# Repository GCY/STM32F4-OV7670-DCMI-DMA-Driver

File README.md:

# STM32F4-Discovery-OV7670-DCMI-DMA-Driver

STM32F429-DISCO+OV7670 MAC and Linux project with arm-none-eabi-gcc, it is modified from [Individální projekty MPOA](http://www.urel.feec.vutbr.cz/MPOA/2014/cam-ov7670) Keil-C project.

I use the same parameters of OV7670 as STM32F429, but the color will be wrong in my design, maybe the problem is exposure, gain, high-speed clock-signal layout? that is my issue list. [to be fix.](https://www.arducam.com/rgb565-format-issues/)

## DCMI Configuration
| STM32F407 | STM32F429 | OV7670 |
| :----: | :----: | :----: |
| 3V3 | 3V3 | RESET |
| GND | GND | PWDN |
| PC6 | PC6 | D0 |
| PC7 | PC7 | D1 |
| PE0 | PC8 | D2 |
| PE1 | PC9 | D3 |
| PE4 | PE4 | D4 |
| PB6 | PB6 | D5 |
| PE5 | PE5 | D6 |
| PE6 | PE6 | D7 |
| PA8 | PA8 | XCLK |
| PA6 | PA6 | PCLK |
| PA4 | PA4 | HREF |
| PB7 | PB7 | VSYNC |
| PB9 | PB9 | SIOD |
| PB8 | PB8 | SIOC |
| GND | GND | GND |
| 3V3 | 3V3 | 3V3 |

## Build

 1. cd .STM32F429-Discovery-OV7670-DCMI-DMA-Driver/STM32F429 Version/firmware/stm32F429-OV7670 & make
 2. load *.elf file with arm-none-eabi-gdb
 3. run

## Test

 1. First, power on and initialize STM32F429 OV7670 SCCB bus.
 2. When the LCD progress bar is complete, OV7670 SCCB command are initialized.
 3. Push "User" button.
 4. STM32F429 capture frame and display to LCD.

Licensing
=======
Copyright (C) 2020  TonyGUO <https://github.com/GCY>.

This program is free software: you can redistribute it and/or modify
it under the terms of the GNU General Public License as published by
the Free Software Foundation, either version 3 of the License, or
(at your option) any later version.

This program is distributed in the hope that it will be useful,
but WITHOUT ANY WARRANTY; without even the implied warranty of
MERCHANTABILITY or FITNESS FOR A PARTICULAR PURPOSE.  See the
GNU General Public License for more details.

You should have received a copy of the GNU General Public License
along with this program.  If not, see <http://www.gnu.org/licenses/>.

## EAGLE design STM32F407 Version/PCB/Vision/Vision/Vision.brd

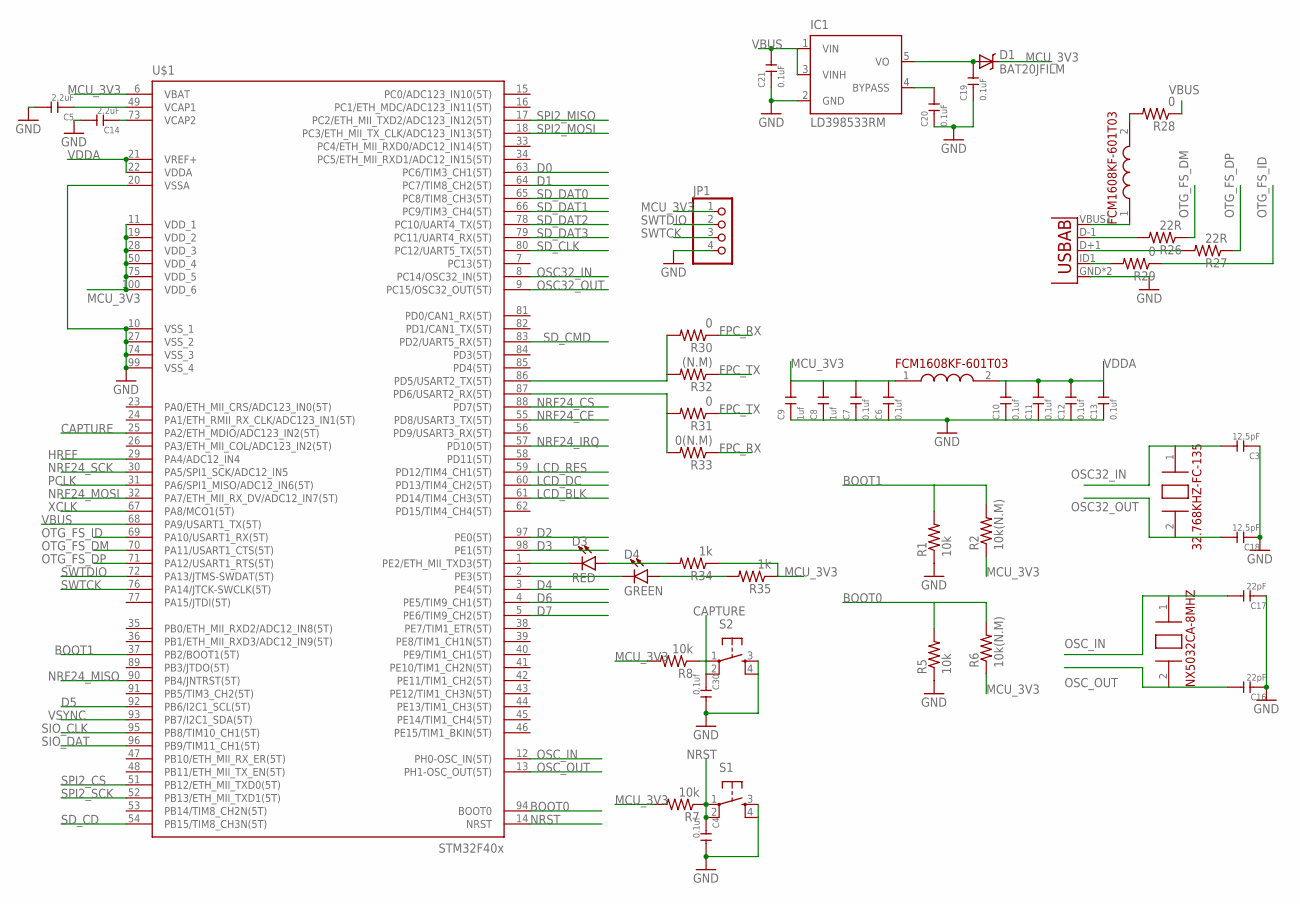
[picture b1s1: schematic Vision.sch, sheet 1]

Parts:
C3, C18: 12.5pF; C0603
C4, C6, C7, C10, C11, C12, C13, C30: 0.1uf; C0603
C5, C14: 2.2uF; C0603
C8, C9: 1uf; C0603
C16, C17: 22pF; C0603
C19, C20, C21: 0.1uF; C0603
D1: BAT20JFILM; SOD-323
D3: RED; LED-0603
D4: GREEN; LED-0603
IC1: LD398533RM; SOT23-5L
JP1: PINHD-1X4; 1X04
R1, R5, R7, R8: 10k; 0603
R2, R6: 10k(N.M); 0603
R26, R27: 22R; 0603-RES
R28, R29: 0; 0603-RES
R30, R31: 0; 0603
R32: (N.M); 0603
R33: 0(N.M); 0603
R34, R35: 1k; 0603
S1, S2: TAC_SWITCHSMD; TACTILE_SWITCH_SMD
U4: USB""; USB-MICRO-SMD
U$1: STM32F407V; TQFP100
U$2: NX5032CA-8MHZ
U$3, U$5: FCM1608KF-601T03
U$4: 32.768KHZ-FC-135

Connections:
BOOT0: R5.2, R6.2, U$1.94 (BOOT0)
BOOT1: R1.2, R2.2, U$1.37 (PB2/BOOT1(5T))
CAPTURE: C30.1, R8.1, S2.1, S2.2, U$1.25 (PA2/ETH_MDIO/ADC123_IN2(5T))
D0: U$1.63 (PC6/TIM3_CH1(5T)); also elsewhere on the board
D1: U$1.64 (PC7/TIM8_CH2(5T)); also elsewhere on the board
D2: U$1.97 (PE0(5T)); also elsewhere on the board
D3: U$1.98 (PE1(5T)); also elsewhere on the board
D4: U$1.3 (PE4(5T)); also elsewhere on the board
D5: U$1.92 (PB6/I2C1_SCL(5T)); also elsewhere on the board
D6: U$1.4 (PE5/TIM9_CH1(5T)); also elsewhere on the board
D7: U$1.5 (PE6/TIM9_CH2(5T)); also elsewhere on the board
FPC_RX: R30.1, R33.1; also elsewhere on the board
FPC_TX: R31.1, R32.1; also elsewhere on the board
GND: C3.1, C4.2, C5.2, C6.1, C7.1, C8.1, C9.1, C10.1, C11.1, C12.1, C13.1, C14.2, C16.1, C17.1, C18.1, C19.1, C20.1, C21.1, C30.2, IC1.2 (GND), JP1.4, R1.1, R5.1, S1.3, S1.4, S2.3, S2.4, U4.GND, U4.GND1 (GND), U$1.10 (VSS_1), U$1.20 (VSSA), U$1.27 (VSS_2), U$1.74 (VSS_3), U$1.99 (VSS_4); also elsewhere on the board
HREF: U$1.29 (PA4/ADC12_IN4); also elsewhere on the board
LCD_BLK: U$1.61 (PD14/TIM4_CH3(5T)); also elsewhere on the board
LCD_DC: U$1.60 (PD13/TIM4_CH2(5T)); also elsewhere on the board
LCD_RES: U$1.59 (PD12/TIM4_CH1(5T)); also elsewhere on the board
MCU_3V3: C6.2, C7.2, C8.2, C9.2, D1.1 (C), JP1.1, R2.1, R6.1, R7.2, R8.2, R34.1, R35.1, U$1.6 (VBAT), U$1.11 (VDD_1), U$1.19 (VDD_2), U$1.28 (VDD_3), U$1.50 (VDD_4), U$1.75 (VDD_5), U$1.100 (VDD_6), U$3.1 (1.IN); also elsewhere on the board
unnamed: D3.C, U$1.1 (PE2/ETH_MII_TXD3(5T))
unnamed: D4.C, U$1.2 (PE3(5T))
unnamed: D3.A, R34.2
unnamed: C5.1, U$1.49 (VCAP1)
unnamed: C14.1, U$1.73 (VCAP2)
unnamed: D4.A, R35.2
unnamed: C20.2, IC1.4 (BYPASS)
unnamed: R26.2, U4.D-1 (D-)
unnamed: C19.2, D1.2 (A), IC1.5 (VO)
unnamed: R27.2, U4.D+1 (D+)
unnamed: U4.VBUS1 (VBUS), U$5.1 (1.IN)
unnamed: R29.2, U4.ID1 (USBID)
unnamed: R28.2, U$5.2 (2.OUT)
NRF24_CE: U$1.55 (PD8/USART3_TX(5T)); also elsewhere on the board
NRF24_CS: U$1.88 (PD7(5T)); also elsewhere on the board
NRF24_IRQ: U$1.57 (PD10(5T)); also elsewhere on the board
NRF24_MISO: U$1.90 (PB4/JNTRST(5T)); also elsewhere on the board
NRF24_MOSI: U$1.32 (PA7/ETH_MII_RX_DV/ADC12_IN7(5T)); also elsewhere on the board
NRF24_SCK: U$1.30 (PA5/SPI1_SCK/ADC12_IN5); also elsewhere on the board
NRST: C4.1, R7.1, S1.1, S1.2, U$1.14 (NRST)
OSC32_IN: C3.2, U$1.8 (PC14/OSC32_IN(5T)), U$4.1 (1.XIN)
OSC32_OUT: C18.2, U$1.9 (PC15/OSC32_OUT(5T)), U$4.2 (2.XIN)
OSC_IN: C17.2, U$1.12 (PH0-OSC_IN(5T)), U$2.1 (1.XIN)
OSC_OUT: C16.2, U$1.13 (PH1-OSC_OUT(5T)), U$2.2 (2.XOUT)
OTG_FS_DM: R26.1, U$1.70 (PA11/USART1_CTS(5T))
OTG_FS_DP: R27.1, U$1.71 (PA12/USART1_RTS(5T))
OTG_FS_ID: R29.1, U$1.69 (PA10/USART1_RX(5T))
PCLK: U$1.31 (PA6/SPI1_MISO/ADC12_IN6(5T)); also elsewhere on the board
SD_CD: U$1.54 (PB15/TIM8_CH3N(5T)); also elsewhere on the board
SD_CLK: U$1.80 (PC12/UART5_TX(5T)); also elsewhere on the board
SD_CMD: U$1.83 (PD2/UART5_RX(5T)); also elsewhere on the board
SD_DAT0: U$1.65 (PC8/TIM8_CH3(5T)); also elsewhere on the board
SD_DAT1: U$1.66 (PC9/TIM3_CH4(5T)); also elsewhere on the board
SD_DAT2: U$1.78 (PC10/UART4_TX(5T)); also elsewhere on the board
SD_DAT3: U$1.79 (PC11/UART4_RX(5T)); also elsewhere on the board
SIO_CLK: U$1.95 (PB8/TIM10_CH1(5T)); also elsewhere on the board
SIO_DAT: U$1.96 (PB9/TIM11_CH1(5T)); also elsewhere on the board
SPI2_CS: U$1.51 (PB12/ETH_MII_TXD0(5T)); also elsewhere on the board
SPI2_MISO: U$1.17 (PC2/ETH_MII_TXD2/ADC123_IN12(5T)); also elsewhere on the board
SPI2_MOSI: U$1.18 (PC3/ETH_MII_TX_CLK/ADC123_IN13(5T)); also elsewhere on the board
SPI2_SCK: U$1.52 (PB13/ETH_MII_TXD1(5T)); also elsewhere on the board
SWTCK: JP1.3, U$1.76 (PA14/JTCK-SWCLK(5T))
SWTDIO: JP1.2, U$1.72 (PA13/JTMS-SWDAT(5T))
UART2_RX: R31.2, R33.2, U$1.87 (PD6/USART2_RX(5T))
UART2_TX: R30.2, R32.2, U$1.86 (PD5/USART2_TX(5T))
VBUS: C21.2, IC1.1 (VIN), IC1.3 (VINH), R28.1, U$1.68 (PA9/USART1_TX(5T))
VDDA: C10.2, C11.2, C12.2, C13.2, U$1.21 (VREF+), U$1.22 (VDDA), U$3.2 (2.OUT)
VSYNC: U$1.93 (PB7/I2C1_SDA(5T)); also elsewhere on the board
XCLK: U$1.67 (PA8/MCO1(5T)); also elsewhere on the board

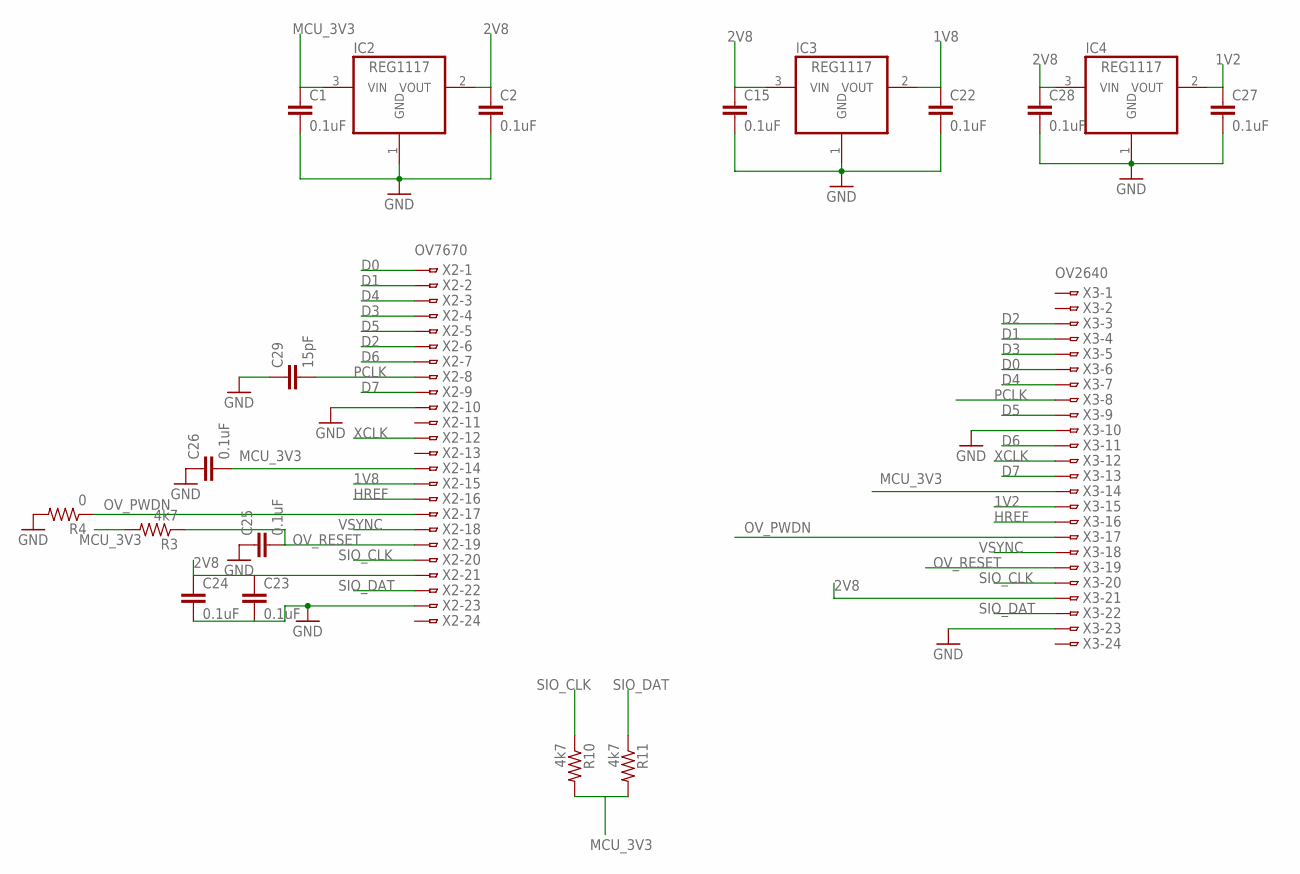
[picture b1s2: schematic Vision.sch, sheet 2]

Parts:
C1, C2, C15, C22, C23, C24, C25, C26, C27, C28: 0.1uF; 0805
C29: 15pF; 0805
IC2, IC3, IC4: REG1117; SOT223
R3, R10, R11: 4k7; 0603
R4: 0; 0603
X2: OV7670; FH12-24S-0.5SH
X3: OV2640; FH12-24S-0.5SH

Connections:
1V2: C27.1, IC4.2 (VOUT), X3.15
1V8: C22.1, IC3.2 (VOUT), X2.15
2V8: C2.1, C15.1, C23.1, C24.1, C28.1, IC2.2 (VOUT), IC3.3 (VIN), IC4.3 (VIN), X2.21, X3.21
D0: X2.1, X3.6; also elsewhere on the board
D1: X2.2, X3.4; also elsewhere on the board
D2: X2.6, X3.3; also elsewhere on the board
D3: X2.4, X3.5; also elsewhere on the board
D4: X2.3, X3.7; also elsewhere on the board
D5: X2.5, X3.9; also elsewhere on the board
D6: X2.7, X3.11; also elsewhere on the board
D7: X2.9, X3.13; also elsewhere on the board
GND: C1.2, C2.2, C15.2, C22.2, C23.2, C24.2, C25.1, C26.1, C27.2, C28.2, C29.1, IC2.1 (GND), IC3.1 (GND), IC4.1 (GND), R4.2, X2.10, X2.23, X3.10, X3.23; also elsewhere on the board
HREF: X2.16, X3.16; also elsewhere on the board
MCU_3V3: C1.1, C26.2, IC2.3 (VIN), R3.2, R10.2, R11.2, X2.14, X3.14; also elsewhere on the board
OV_PWDN: R4.1, X2.17, X3.17
OV_RESET: C25.2, R3.1, X2.19, X3.19
PCLK: C29.2, X2.8, X3.8; also elsewhere on the board
SIO_CLK: R10.1, X2.20, X3.20; also elsewhere on the board
SIO_DAT: R11.1, X2.22, X3.22; also elsewhere on the board
VSYNC: X2.18, X3.18; also elsewhere on the board
XCLK: X2.12, X3.12; also elsewhere on the board

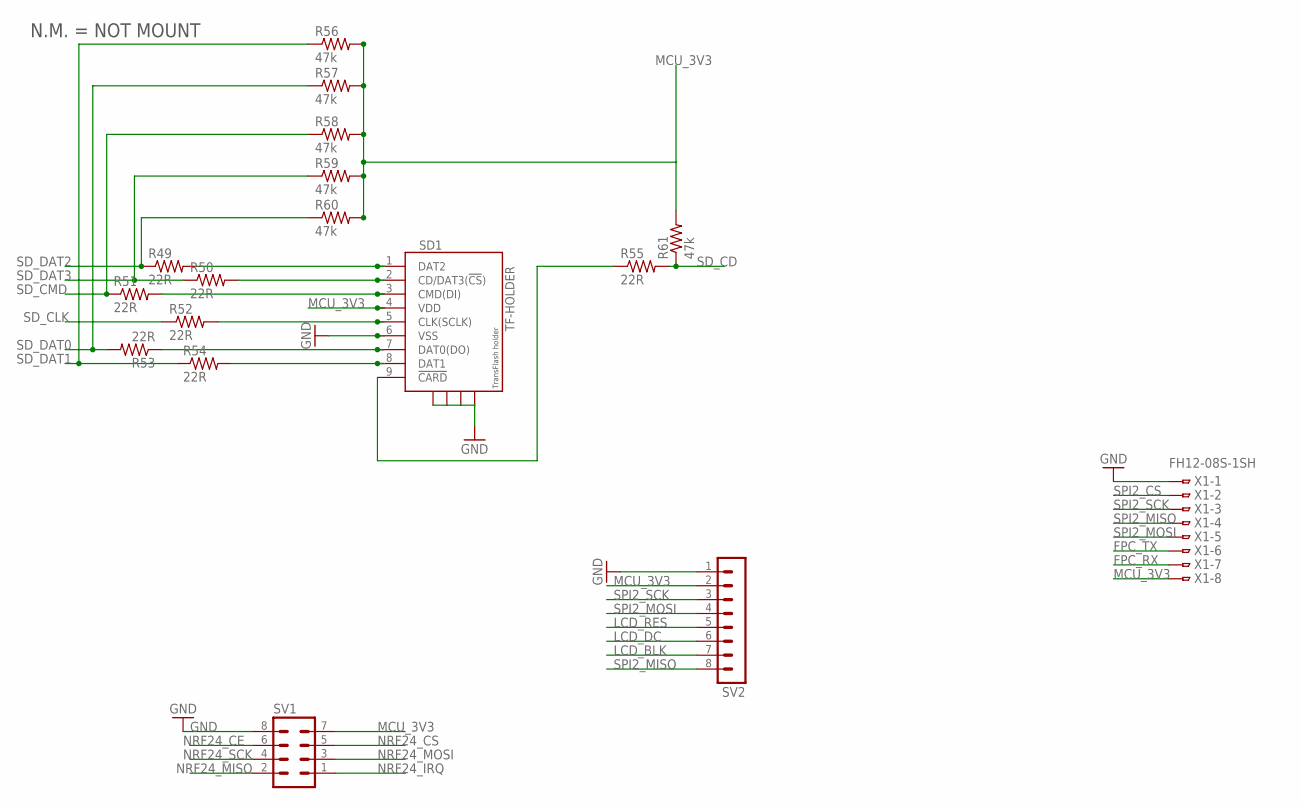
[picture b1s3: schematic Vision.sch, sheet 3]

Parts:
R49, R50, R51, R52, R53, R54, R55: 22R; 0603-RES
R56, R57, R58, R59, R60, R61: 47k; 0603-RES
SD1: TF-HOLDER; TF-PULL
SV1: MA04-2
SV2: MA08-1
X1: FH12-08S-1SH

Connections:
FPC_RX: X1.7; also elsewhere on the board
FPC_TX: X1.6; also elsewhere on the board
GND: SD1.6 (VSS), SD1.S1, SD1.S2, SD1.S3, SD1.S4, SV1.8, SV2.1, X1.1; also elsewhere on the board
LCD_BLK: SV2.7; also elsewhere on the board
LCD_DC: SV2.6; also elsewhere on the board
LCD_RES: SV2.5; also elsewhere on the board
MCU_3V3: R56.2, R57.2, R58.2, R59.2, R60.2, R61.2, SD1.4 (VDD), SV1.7, SV2.2, X1.8; also elsewhere on the board
unnamed: R49.2, SD1.1 (DAT2)
unnamed: R50.2, SD1.2 (CD/DAT3(!CS!))
unnamed: R51.2, SD1.3 (CMD(DI))
unnamed: R52.2, SD1.5 (CLK(SCLK))
unnamed: R53.1, SD1.7 (DAT0(DO))
unnamed: R54.2, SD1.8 (DAT1)
unnamed: R55.1, SD1.9 (!CARD)
NRF24_CE: SV1.6; also elsewhere on the board
NRF24_CS: SV1.5; also elsewhere on the board
NRF24_IRQ: SV1.1; also elsewhere on the board
NRF24_MISO: SV1.2; also elsewhere on the board
NRF24_MOSI: SV1.3; also elsewhere on the board
NRF24_SCK: SV1.4; also elsewhere on the board
SD_CD: R55.2, R61.1; also elsewhere on the board
SD_CLK: R52.1; also elsewhere on the board
SD_CMD: R51.1, R58.1; also elsewhere on the board
SD_DAT0: R53.2, R57.1; also elsewhere on the board
SD_DAT1: R54.1, R56.1; also elsewhere on the board
SD_DAT2: R49.1, R60.1; also elsewhere on the board
SD_DAT3: R50.1, R59.1; also elsewhere on the board
SPI2_CS: X1.2; also elsewhere on the board
SPI2_MISO: SV2.8, X1.4; also elsewhere on the board
SPI2_MOSI: SV2.4, X1.5; also elsewhere on the board
SPI2_SCK: SV2.3, X1.3; also elsewhere on the board

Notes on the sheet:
N.M. = NOT MOUNT

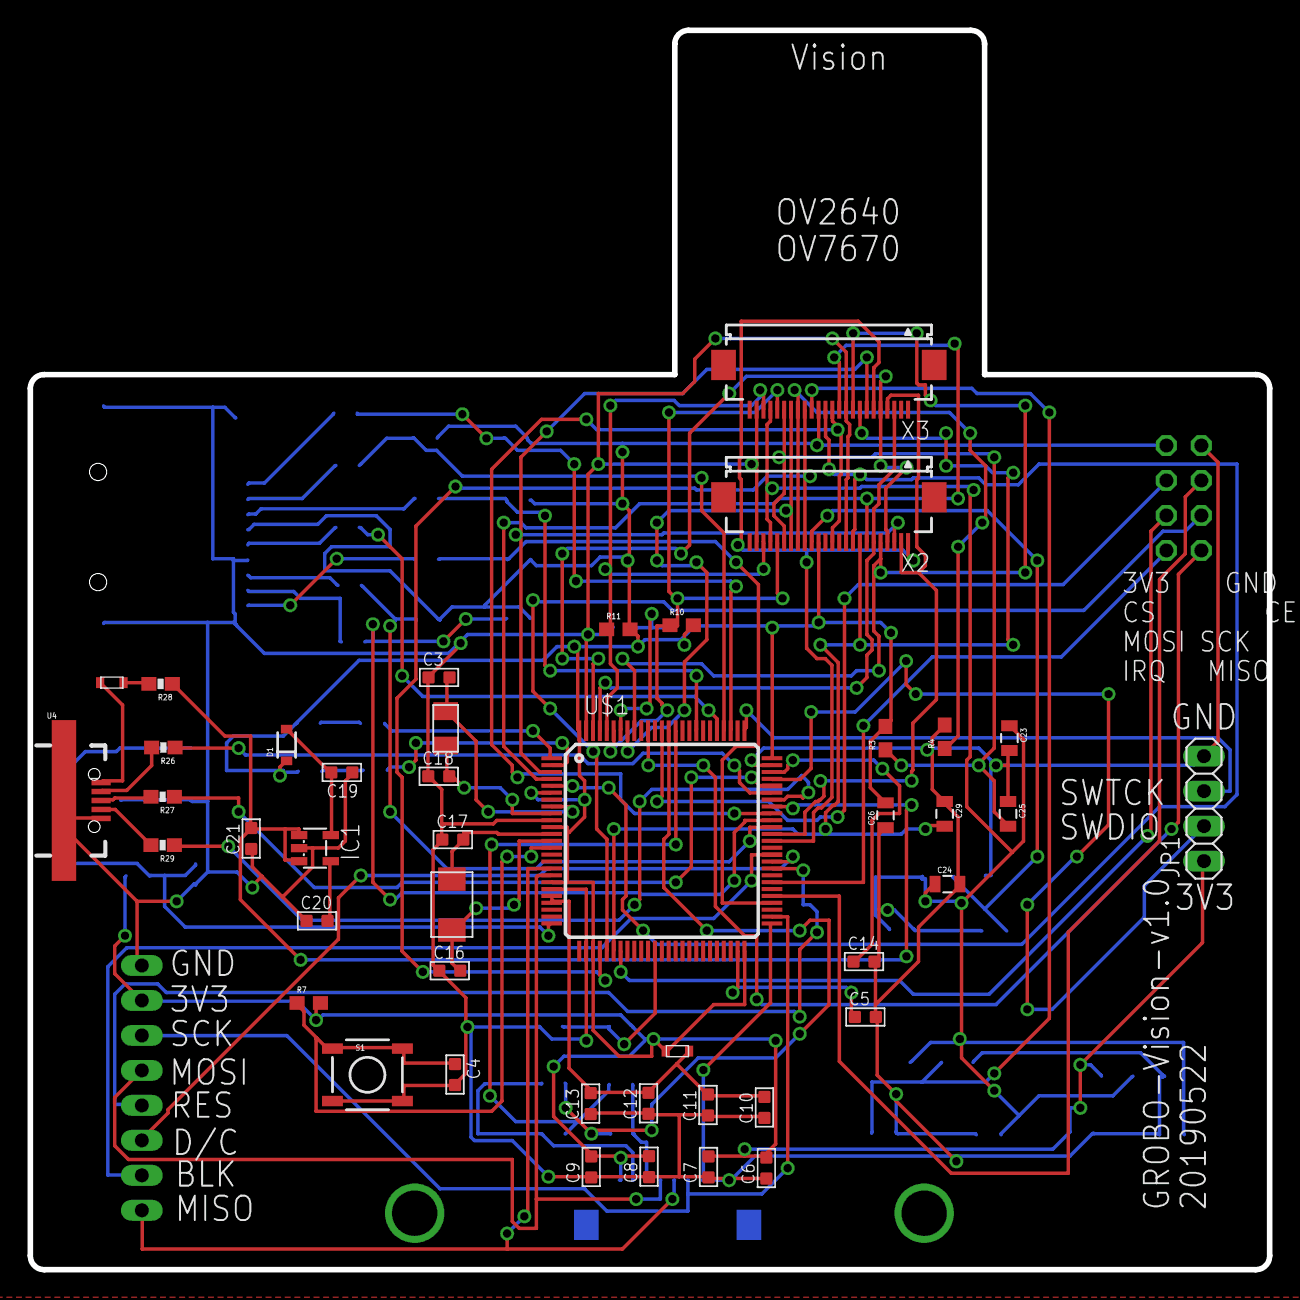
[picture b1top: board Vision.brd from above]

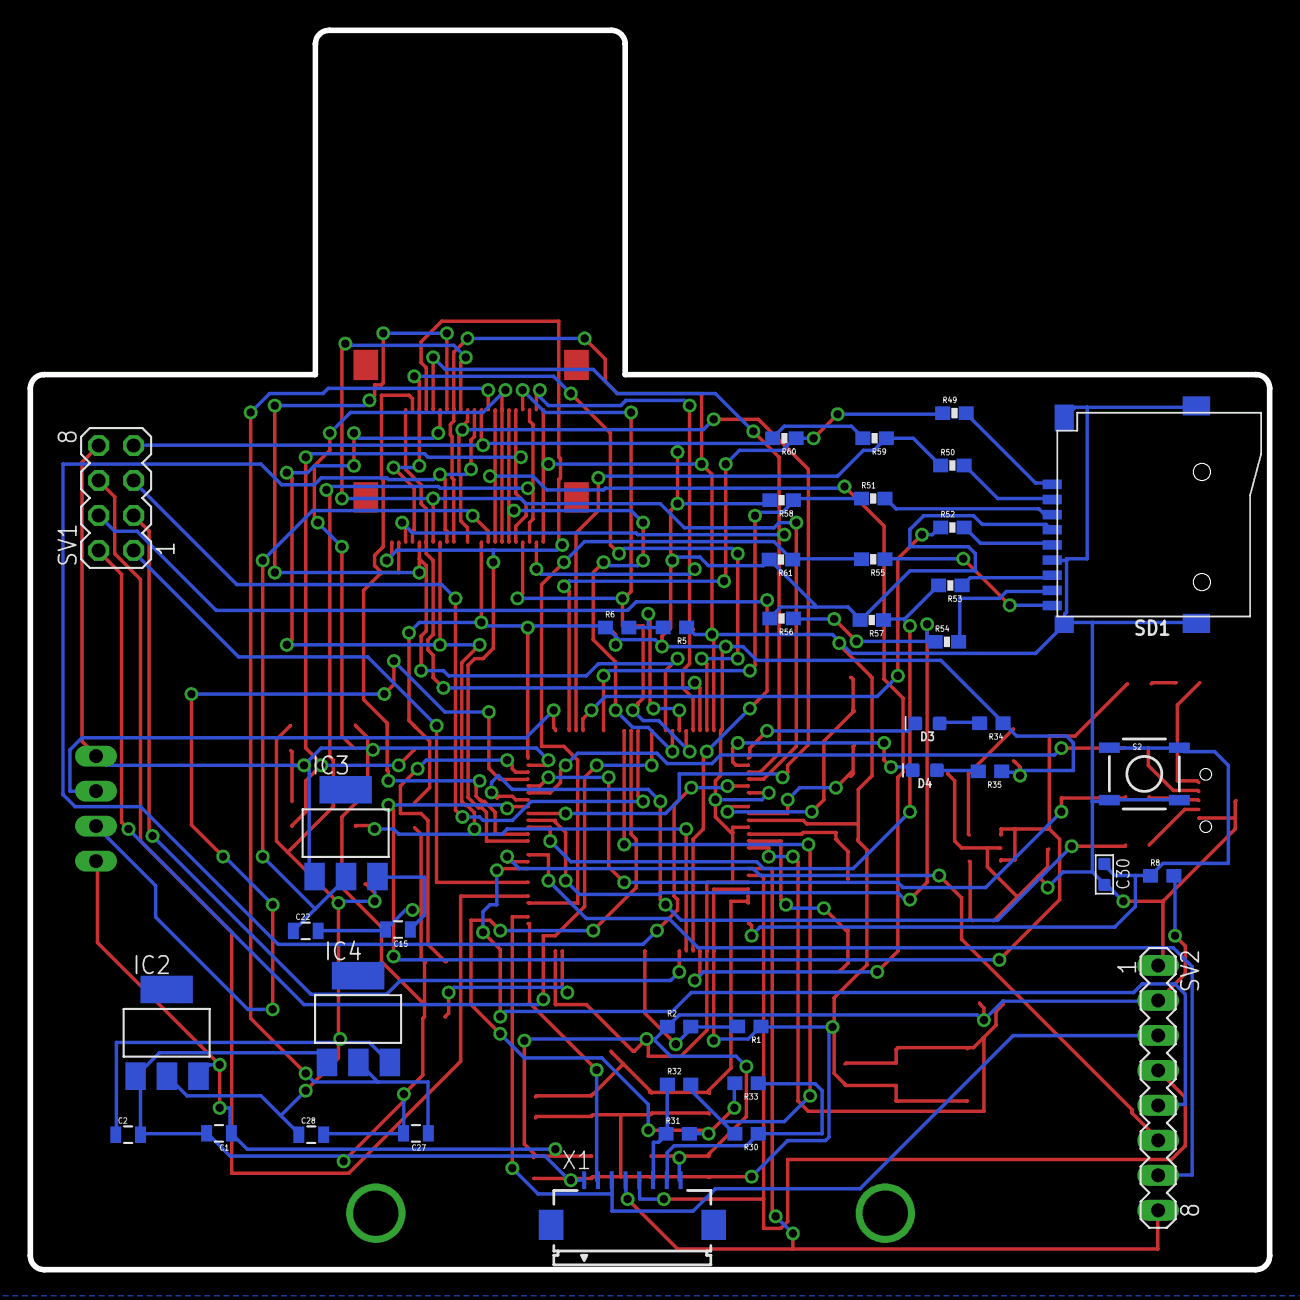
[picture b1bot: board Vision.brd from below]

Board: 2 copper layers, 90.0 x 90.0 mm, 85 parts (41 on the bottom side), 80 nets.

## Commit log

2020-05-25 arm-none-eabi-gcc toolchain successful build
2020-05-25 demo.gif
2020-05-26 move folder to stm32f429 version
2020-05-26 rename
2020-05-27 STM32F407 version
2020-05-27 PCB V1

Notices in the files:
parts and their libraries:
SparkFun-DiscreteSemi: Licensing: CC v3.0 Share-Alike You are welcome to use this library for commercial purposes.
